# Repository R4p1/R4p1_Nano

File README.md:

# R4p1_Nano

## Overview
- Arduino Nano Compatible
## Requirement
### Development
- KiCad8.0
### Boards
- "Platform Name, Board Name, etc..."
### Libraries
- "Library Name and Version used in this repository"

## Usage
- Use as Arduino Nano compatible

## Features
- "Detailed Description"

## Reference
- ["Reference Site Name"]("Reference URL")

## Author
- [R4p1](https://github.com/R4p1)

## License
- (C) 2024 R4p1

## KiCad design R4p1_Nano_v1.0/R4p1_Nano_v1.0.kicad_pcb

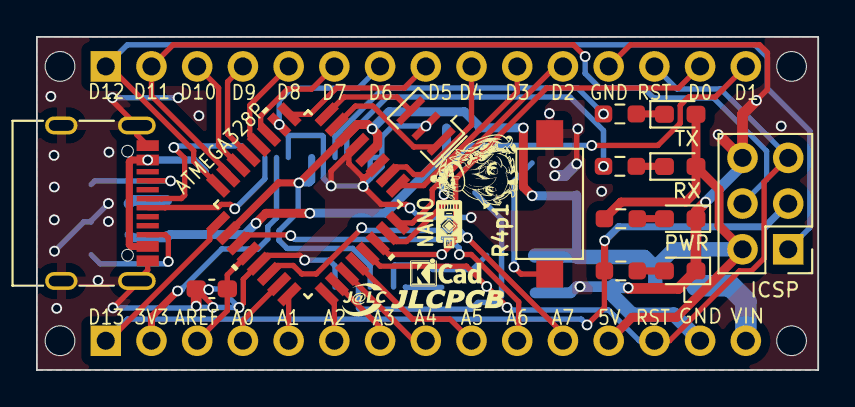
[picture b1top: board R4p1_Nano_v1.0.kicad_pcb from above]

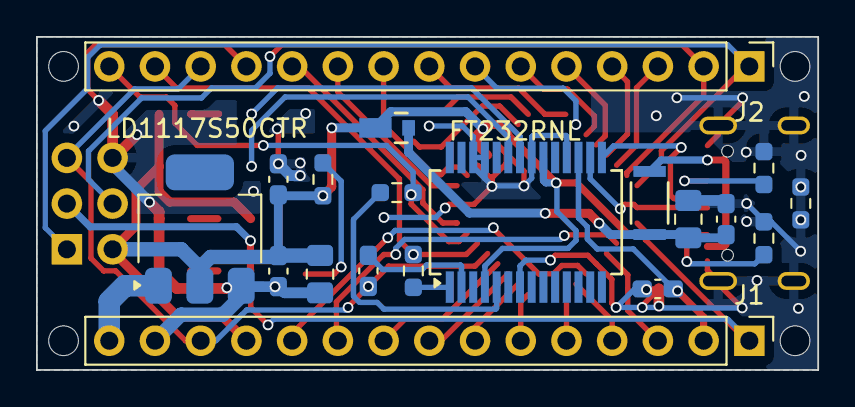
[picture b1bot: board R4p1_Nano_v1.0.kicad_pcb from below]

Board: 2 copper layers, 43.4 x 18.5 mm, 37 parts (19 on the bottom side), 46 nets.

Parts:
16MHz: 16MHz; Resonator_SMD_Murata_CSTxExxV-3Pin_3.0x1.1mm
ATMEGA328P: ATMEGA328P-AU; TQFP32_32A_MCH
C1, C3: 1u; C_0603_1608Metric_Pad1.08x0.95mm_HandSolder
C2, C9: 4.7u; C_0805_2012Metric_Pad1.18x1.45mm_HandSolder
C5, C6, C7, C8: 100n; C_0603_1608Metric_Pad1.08x0.95mm_HandSolder
D1: CUHS20S30_H3F; US2H_TOS
FT232RNL: FT232RL; SSOP-28_5.3x10.2mm_P0.65mm
ICSP: Conn_02x03_Odd_Even; PinHeader_2x03_P2.54mm_Vertical
J1: Analog; PinHeader_1x15_P2.54mm_Vertical
J2: Digital; PinHeader_1x15_P2.54mm_Vertical
J4: USB_C_Receptacle_USB2.0_14P; USB_C_Receptacle_G-Switch_GT-USB-7010ASV
L: YELLOW; LED_0603_1608Metric_Pad1.05x0.95mm_HandSolder
LD1117S50CTR: LD1117S50CTR; SOT-223
MH1, MH2, MH3, MH4: MountingHole_65mil
PWR: GREEN; LED_0603_1608Metric_Pad1.05x0.95mm_HandSolder
R1, R2, R3, R4, R5, R7, R9, R10: 1k; R_0603_1608Metric_Pad0.98x0.95mm_HandSolder
R6, R8: 5.1k; R_0603_1608Metric_Pad0.98x0.95mm_HandSolder
RX: RED; LED_0603_1608Metric_Pad1.05x0.95mm_HandSolder
SW1: SW_Push; SW_SPST_CK_RS282G05A3
TX: GREEN; LED_0603_1608Metric_Pad1.05x0.95mm_HandSolder
U4: MF-NSMF050-2; CHIP_NSMF050_3P4XP18

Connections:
*D3: ATMEGA328P.1 (PD3(PCINT19/OC2B/INT1)), J2.10
*D5: ATMEGA328P.9 (PD5(PCINT21/OC0B/T1)), J2.8
*D6: ATMEGA328P.10 (PD6(PCINT22/OC0A/AIN0)), J2.7
*D9: ATMEGA328P.13 (PB1(PCINT1/OC1A)), J2.4
*D10/SS: ATMEGA328P.14 (PB2(PCINT2/*SS/OC1B)), J2.3
*D11/MOSI: ATMEGA328P.15 (PB3(PCINT3/OC2A/MOSI)), ICSP.4, J2.2
+3V3: C7.2, FT232RNL.17 (3V3OUT), J1.2
+5V: ATMEGA328P.4 (VCC), ATMEGA328P.6 (VCC), ATMEGA328P.18 (AVCC), C1.2, C3.2, C9.1, D1.1 (CATHODE), FT232RNL.4 (VCCIO), FT232RNL.20 (VCC), ICSP.2, J1.12, LD1117S50CTR.2 (VOUT), R1.2, R2.1, RX.2 (A), TX.2 (A)
/AREF: ATMEGA328P.20 (AREF), C6.2, J1.3
/D0/RX: ATMEGA328P.30 (PD0(RXD/PCINT16)), J2.14, R5.2
/D1/TX: ATMEGA328P.31 (PD1(TXD/PCINT17)), J2.15, R4.1
A0: ATMEGA328P.23 (PC0(ADC0/PCINT8)), J1.4
A1: ATMEGA328P.24 (PC1(ADC1/PCINT9)), J1.5
A2: ATMEGA328P.25 (PC2(ADC2/PCINT10)), J1.6
A3: ATMEGA328P.26 (PC3(ADC3/PCINT11)), J1.7
A4/SDA: ATMEGA328P.27 (PC4(ADC4/SDA/PCINT12)), J1.8
A5/SCL: ATMEGA328P.28 (PC5(ADC5/SCL/PCINT13)), J1.9
A6: ATMEGA328P.19 (ADC6), J1.10
A7: ATMEGA328P.22 (ADC7), J1.11
D2: ATMEGA328P.32 (PD2(INT0/PCINT18)), J2.11
D4: ATMEGA328P.2 (PD4(PCINT20/XCK/T0)), J2.9
D7: ATMEGA328P.11 (PD7(PCINT23/AIN1)), J2.6
D8: ATMEGA328P.12 (PB0(PCINT0/CLKO/ICP1)), J2.5
D12/MISO: ATMEGA328P.16 (PB4(PCINT4/MISO)), ICSP.1, J2.1
D13/SCK: ATMEGA328P.17 (PB5(SCK/PCINT5)), ICSP.3, J1.1, R3.1
GND: 16MHz.2, ATMEGA328P.3 (GND), ATMEGA328P.5 (GND), ATMEGA328P.21 (GND), C1.1, C2.2, C3.1, C5.1, C6.1, C7.1, C9.2, FT232RNL.7 (GND), FT232RNL.18 (GND), FT232RNL.21 (GND), FT232RNL.25 (AGND), FT232RNL.26 (TEST), ICSP.6, J1.14, J2.12, J4.A1 (GND), J4.A12 (GND), J4.B1 (GND), J4.B12 (GND), J4.S1 (SHIELD), L.1 (K), LD1117S50CTR.3 (VIN), PWR.1 (K), R6.1, R7.1, R7.2, R8.2, SW1.1
unnamed: J4.A5 (CC1), R8.1
unnamed: J4.B5 (CC2), R6.2
unnamed: J4.A4 (VBUS), J4.A9 (VBUS), J4.B4 (VBUS), J4.B9 (VBUS), U4.1
unnamed: L.2 (A), R3.2
unnamed: PWR.2 (A), R2.2
unnamed: R1.1, SW1.2
unnamed: R9.1, RX.1 (K)
unnamed: R10.1, TX.1 (K)
unnamed: 16MHz.1, ATMEGA328P.7 (PB6(PCINT6/XTAL1/TOSC1))
unnamed: 16MHz.3, ATMEGA328P.8 (PB7(PCINT7/XTAL2/TOSC2))
unnamed: FT232RNL.23 (CBUS0), R9.2
unnamed: FT232RNL.22 (CBUS1), R10.2
unnamed: C8.1, FT232RNL.2 (DTR)
unnamed: FT232RNL.15 (USBD+), J4.A6 (D+)
unnamed: FT232RNL.16 (USBD-), J4.A7 (D-)
RX: FT232RNL.1 (TXD), R5.1
TX: FT232RNL.5 (RXD), R4.2
VIN: J1.15, LD1117S50CTR.1 (ADJ/GND)
VUSB: C2.1, C5.2, D1.2 (ANODE), U4.2
~RESET: ATMEGA328P.29 (PC6(*RESET/PCINT14)), C8.2, ICSP.5, J1.13, J2.13

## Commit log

2024-11-04 Initialize main
2024-11-04 upload R4p1_Nano
2024-11-04 upload R4p1-Nano-gerber file
